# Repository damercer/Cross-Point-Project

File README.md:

# Cross Point Project
Software-Configured Breadboard Hardware Targeting Circuit Wiring Error Reduction in ECE Labs.
#
Abstract:
#
The hardware project aims to examine the effectiveness of software-configured wiring compared to traditional manual wiring of breadboards. While both methods use actual hardware, the software-configured approach automates the connections between components, thereby minimizing wiring errors and setup time. The intent is to investigate the impact of each approach on student comprehension, engagement, and error rates. By comparing these two approaches, the project seeks to determine which method better supports student engagement, educational outcomes and reduces frustration associated with complex circuit construction.
#
Introduction:
#
Hands-on experiential learning is a cornerstone of ECE education, typically relying on manual wiring of circuits on solderless breadboards. Using a traditional solderless breadboard as the means for building electronic circuit lab experiments requires the student, in addition to placing components, to manually insert wires to connect together the component pins according to a schematic diagram. These manual translation steps from schematic to hardware can lead to wiring errors in the experimental setup that can obscure circuit principles. While this manual wiring method offers valuable experience in physical component handling and troubleshooting, the extra time needed for debugging and correcting these errors leads to frustration and loss of precious lab time to investigate the circuit concept in question.

The goal is to evaluate the educational benefits and potential drawbacks of these software-configured hardware systems compared to traditional manual wiring. By doing so, it addresses the need for balancing hands-on skills with error minimization and conceptual understanding in electrical engineering education.
#
Analog switch matrix cross point experiment breadboard.
#

Prototype PCB (Red version)
 
The idea is to computerize the wiring of the breadboard in an effort to reduce student frustration when building complex experiments. Using four analog 16X8 cross point switches wired together into two 32X8 cross points with a fifth switch matrix interconnecting the two smaller arrays into effectively a single 64X16 array.

This breadboard makes real, hardware connections between the 64 breadboard component pins on the board to the16 “jumper” nodes on the board via software commands, instead of needing to manually install jumper wires. The prototype PCB is shown, figure 1, which incorporates two mini 170 pin solderless breadboards, one for each of the 32X8 cross point arrays. There are a combined 68 total component pin locations across both mini breadboards with power distribution strips top and bottom. The two mini breadboards connect to the PCB through pogo pins and so they can be easily removed. It would then be possible to bolt on custom daughter PCBs with whatever components are needed for a given course already installed. Such as CMOS transistor arrays (CD4007) with even some pre-wired sub-circuits like current sources and OTAs.

The combined 64X16 cross point matrix board uses a total of 5 CH446DS 16X8 analog cross point ICs (from China) programed via a RP-2040 micro controller breakout board (Pi Pico or equivalent). Materials cost per board, in quantities of 10 or more, is less than $30 not including the assembly labor.

The board is powered from the Pi Pico USB connection. For powering the experiment circuits, male Pin Jumpers can be set for 0 and +3.3V, 0 and +5V or -5V and +5V power (or 0 and +10V) using an on board isolated 5V DC-DC generator.

LTspice is used to enter the schematic for the experiment. In addition to the standard library symbols a number of supporting schematic library files have been created. Schematic symbols for TO-92 transistors and resistors of various lead spacing are available in the LTspice files.

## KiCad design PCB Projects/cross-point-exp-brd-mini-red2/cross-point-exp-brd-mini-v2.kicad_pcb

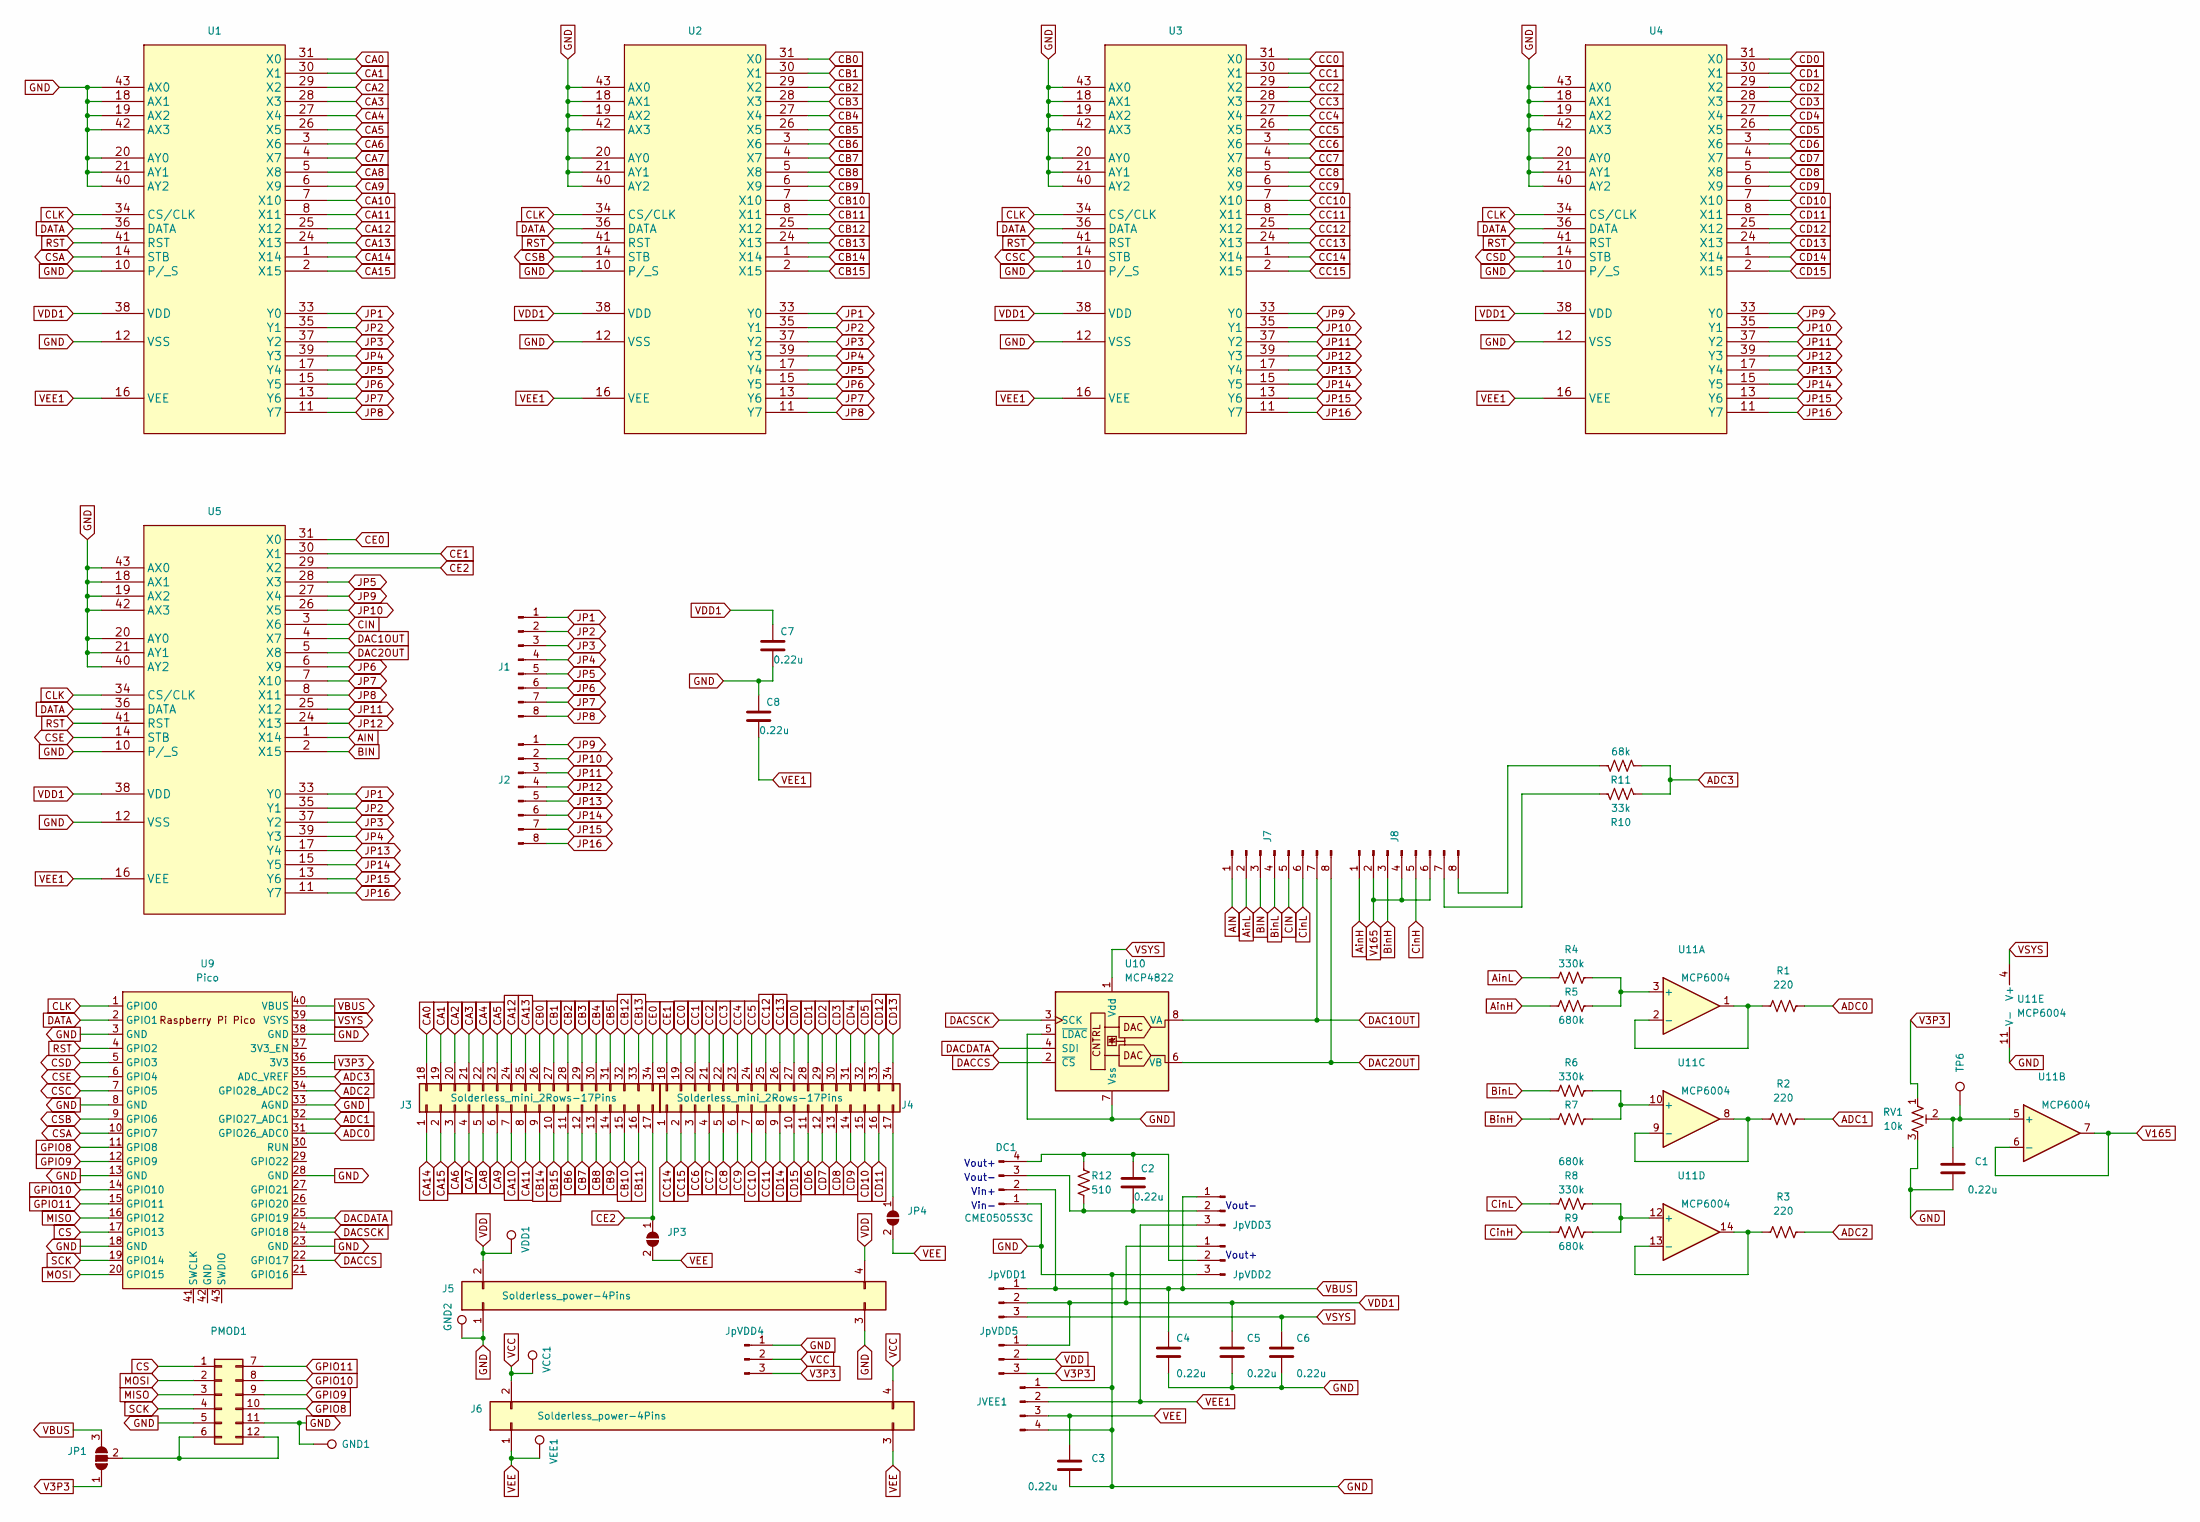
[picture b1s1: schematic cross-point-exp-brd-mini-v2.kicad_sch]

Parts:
C1, C2, C3, C4, C5, C6, C7, C8: 0.22u; C_Rect_L7.0mm_W2.0mm_P5.00mm
DC1: CME0505S3C; PinHeader_1x04_P2.54mm_Vertical
GND1: TestPoint; TestPoint_THTPad_D1.5mm_Drill0.7mm
GND2: TestPoint; TestPoint_THTPad_D2.0mm_Drill1.0mm
J1, J2, J7, J8: Conn_01x08_Pin; PinHeader_1x08_P2.54mm_Vertical
J3, J4: Solderless_mini_2Rows-17Pins; Solderless_mini_th_pogo_2x17_P2.54mm
J5, J6: Solderless_power-4Pins; Solderless_power_2x4_P2.54mm
JP1: SolderJumper_3_Open; SolderJumper-3_P1.3mm_Open_RoundedPad1.0x1.5mm_NumberLabels
JP3, JP4: SolderJumper_2_Open; SolderJumper-2_P1.3mm_Open_RoundedPad1.0x1.5mm
JVEE1: Conn_01x04_Pin; PinHeader_1x04_P2.54mm_Vertical
JpVDD1, JpVDD2, JpVDD3, JpVDD4, JpVDD5: Conn_01x03_Pin; PinHeader_1x03_P2.54mm_Vertical
PMOD1: Conn_02x06_Top_Bottom; PMOD_Header_2x06_P2.54mm
R1, R2, R3: 220; R_Axial_DIN0204_L3.6mm_D1.6mm_P7.62mm_Horizontal
R4, R6, R8: 330k; R_Axial_DIN0204_L3.6mm_D1.6mm_P7.62mm_Horizontal
R5, R7, R9: 680k; R_Axial_DIN0204_L3.6mm_D1.6mm_P7.62mm_Horizontal
R10: 33k; R_Axial_DIN0204_L3.6mm_D1.6mm_P7.62mm_Horizontal
R11: 68k; R_Axial_DIN0204_L3.6mm_D1.6mm_P7.62mm_Horizontal
R12: 510; R_Axial_DIN0204_L3.6mm_D1.6mm_P7.62mm_Horizontal
RV1: 10k; Potentiometer_Bourns_3386P_Vertical
TP6: TestPoint; TestPoint_THTPad_D1.5mm_Drill0.7mm
U1, U2, U3, U4, U5: LQFP44_Tight
U9: Pico; RPi_Pico_SMD_TH
U10: MCP4822; DIP-8_W7.62mm
U11: MCP6004; DIP-14_W7.62mm
VCC1: TestPoint; TestPoint_THTPad_D2.0mm_Drill1.0mm
VDD1: TestPoint; TestPoint_THTPad_D2.0mm_Drill1.0mm
VEE1: TestPoint; TestPoint_THTPad_D2.0mm_Drill1.0mm

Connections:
ADC0: R1.1, U9.31 (GPIO26_ADC0)
ADC1: R2.1, U9.32 (GPIO27_ADC1)
ADC2: R3.1, U9.34 (GPIO28_ADC2)
ADC3: R10.1, R11.1, U9.35 (ADC_VREF)
AIN: J7.1, U5.1 (X14)
AinH: J8.1, R5.2
AinL: J7.2, R4.2
BIN: J7.3, U5.2 (X15)
BinH: J8.3, R7.2
BinL: J7.4, R6.2
CA0: J3.18, U1.31 (X0)
CA1: J3.19, U1.30 (X1)
CA2: J3.20, U1.29 (X2)
CA3: J3.21, U1.28 (X3)
CA4: J3.22, U1.27 (X4)
CA5: J3.23, U1.26 (X5)
CA6: J3.3, U1.3 (X6)
CA7: J3.4, U1.4 (X7)
CA8: J3.5, U1.5 (X8)
CA9: J3.6, U1.6 (X9)
CA10: J3.7, U1.7 (X10)
CA11: J3.8, U1.8 (X11)
CA12: J3.24, U1.25 (X12)
CA13: J3.25, U1.24 (X13)
CA14: J3.1, U1.1 (X14)
CA15: J3.2, U1.2 (X15)
CB0: J3.26, U2.31 (X0)
CB1: J3.27, U2.30 (X1)
CB2: J3.28, U2.29 (X2)
CB3: J3.29, U2.28 (X3)
CB4: J3.30, U2.27 (X4)
CB5: J3.31, U2.26 (X5)
CB6: J3.11, U2.3 (X6)
CB7: J3.12, U2.4 (X7)
CB8: J3.13, U2.5 (X8)
CB9: J3.14, U2.6 (X9)
CB10: J3.15, U2.7 (X10)
CB11: J3.16, U2.8 (X11)
CB12: J3.32, U2.25 (X12)
CB13: J3.33, U2.24 (X13)
CB14: J3.9, U2.1 (X14)
CB15: J3.10, U2.2 (X15)
CC0: J4.19, U3.31 (X0)
CC1: J4.20, U3.30 (X1)
CC2: J4.21, U3.29 (X2)
CC3: J4.22, U3.28 (X3)
CC4: J4.23, U3.27 (X4)
CC5: J4.24, U3.26 (X5)
CC6: J4.3, U3.3 (X6)
CC7: J4.4, U3.4 (X7)
CC8: J4.5, U3.5 (X8)
CC9: J4.6, U3.6 (X9)
CC10: J4.7, U3.7 (X10)
CC11: J4.8, U3.8 (X11)
CC12: J4.25, U3.25 (X12)
CC13: J4.26, U3.24 (X13)
CC14: J4.1, U3.1 (X14)
CC15: J4.2, U3.2 (X15)
CD0: J4.27, U4.31 (X0)
CD1: J4.28, U4.30 (X1)
CD2: J4.29, U4.29 (X2)
CD3: J4.30, U4.28 (X3)
CD4: J4.31, U4.27 (X4)
CD5: J4.32, U4.26 (X5)
CD6: J4.11, U4.3 (X6)
CD7: J4.12, U4.4 (X7)
CD8: J4.13, U4.5 (X8)
CD9: J4.14, U4.6 (X9)
CD10: J4.15, U4.7 (X10)
CD11: J4.16, U4.8 (X11)
CD12: J4.33, U4.25 (X12)
CD13: J4.34, U4.24 (X13)
CD14: J4.9, U4.1 (X14)
CD15: J4.10, U4.2 (X15)
CE0: J3.34, U5.31 (X0)
CE1: J4.18, U5.30 (X1)
CE2: J3.17, JP3.1 (A), U5.29 (X2)
CIN: J7.5, U5.3 (X6)
CLK: U1.34 (CS/CLK), U2.34 (CS/CLK), U3.34 (CS/CLK), U4.34 (CS/CLK), U5.34 (CS/CLK), U9.1 (GPIO0)
CS: PMOD1.1, U9.17 (GPIO13)
CSA: U1.14 (STB), U9.10 (GPIO7)
CSB: U2.14 (STB), U9.9 (GPIO6)
CSC: U3.14 (STB), U9.7 (GPIO5)
CSD: U4.14 (STB), U9.5 (GPIO3)
CSE: U5.14 (STB), U9.6 (GPIO4)
CinH: J8.5, R9.2
CinL: J7.6, R8.2
DAC1OUT: J7.7, U5.4 (X7), U10.8 (VA)
DAC2OUT: J7.8, U5.5 (X8), U10.6 (VB)
DACCS: U9.22 (GPIO17), U10.2 (~CS)
DACDATA: U9.25 (GPIO19), U10.4 (SDI)
DACSCK: U9.24 (GPIO18), U10.3 (SCK)
DATA: U1.36 (DATA), U2.36 (DATA), U3.36 (DATA), U4.36 (DATA), U5.36 (DATA), U9.2 (GPIO1)
GND: C1.2, C3.2, C4.2, C5.2, C6.2, C7.2, C8.1, DC1.1, GND1.1, GND2.1, J5.1, J5.3, JVEE1.1, JVEE1.4, JpVDD2.3, JpVDD4.1, PMOD1.5, PMOD1.11, RV1.3, U1.10 (P/_S), U1.12 (VSS), U1.18 (AX1), U1.19 (AX2), U1.20 (AY0), U1.21 (AY1), U1.40 (AY2), U1.42 (AX3), U1.43 (AX0), U2.10 (P/_S), U2.12 (VSS), U2.18 (AX1), U2.19 (AX2), U2.20 (AY0), U2.21 (AY1), U2.40 (AY2), U2.42 (AX3), U2.43 (AX0), U3.10 (P/_S), U3.12 (VSS), U3.18 (AX1), U3.19 (AX2), U3.20 (AY0), U3.21 (AY1), U3.40 (AY2), U3.42 (AX3), U3.43 (AX0), U4.10 (P/_S), U4.12 (VSS), U4.18 (AX1), U4.19 (AX2), U4.20 (AY0), U4.21 (AY1), U4.40 (AY2), U4.42 (AX3), U4.43 (AX0), U5.10 (P/_S), U5.12 (VSS), U5.18 (AX1), U5.19 (AX2), U5.20 (AY0), U5.21 (AY1), U5.40 (AY2), U5.42 (AX3), U5.43 (AX0), U9.3 (GND), U9.8 (GND), U9.13 (GND), U9.18 (GND), U9.23 (GND), U9.28 (GND), U9.33 (AGND), U9.38 (GND), U10.5 (~LDAC), U10.7 (Vss), U11.11 (V-)
GPIO8: PMOD1.10, U9.11 (GPIO8)
GPIO9: PMOD1.9, U9.12 (GPIO9)
GPIO10: PMOD1.8, U9.14 (GPIO10)
GPIO11: PMOD1.7, U9.15 (GPIO11)
JP1: J1.1, U1.33 (Y0), U2.33 (Y0), U5.33 (Y0)
JP2: J1.2, U1.35 (Y1), U2.35 (Y1), U5.35 (Y1)
JP3: J1.3, U1.37 (Y2), U2.37 (Y2), U5.37 (Y2)
JP4: J1.4, U1.39 (Y3), U2.39 (Y3), U5.39 (Y3)
JP5: J1.5, U1.17 (Y4), U2.17 (Y4), U5.28 (X3)
JP6: J1.6, U1.15 (Y5), U2.15 (Y5), U5.6 (X9)
JP7: J1.7, U1.13 (Y6), U2.13 (Y6), U5.7 (X10)
JP8: J1.8, U1.11 (Y7), U2.11 (Y7), U5.8 (X11)
JP9: J2.1, U3.33 (Y0), U4.33 (Y0), U5.27 (X4)
JP10: J2.2, U3.35 (Y1), U4.35 (Y1), U5.26 (X5)
JP11: J2.3, U3.37 (Y2), U4.37 (Y2), U5.25 (X12)
JP12: J2.4, U3.39 (Y3), U4.39 (Y3), U5.24 (X13)
JP13: J2.5, U3.17 (Y4), U4.17 (Y4), U5.17 (Y4)
JP14: J2.6, U3.15 (Y5), U4.15 (Y5), U5.15 (Y5)
JP15: J2.7, U3.13 (Y6), U4.13 (Y6), U5.13 (Y6)
JP16: J2.8, U3.11 (Y7), U4.11 (Y7), U5.11 (Y7)
MISO: PMOD1.3, U9.16 (GPIO12)
MOSI: PMOD1.2, U9.20 (GPIO15)
unnamed: C2.2, DC1.3, JpVDD3.2, R12.1
unnamed: C2.1, DC1.4, JpVDD2.2, R12.2
unnamed: J4.17, JP4.1 (A)
unnamed: J8.7, R10.2
unnamed: J8.8, R11.2
unnamed: JP1.2 (C), PMOD1.6, PMOD1.12
unnamed: R4.1, R5.1, U11.3 (+)
unnamed: R1.2, U11.1, U11.2 (-)
unnamed: C1.1, RV1.2, TP6.1, U11.5 (+)
unnamed: R6.1, R7.1, U11.10 (+)
unnamed: R2.2, U11.8, U11.9 (-)
unnamed: R8.1, R9.1, U11.12 (+)
unnamed: R3.2, U11.13 (-), U11.14
RST: U1.41 (RST), U2.41 (RST), U3.41 (RST), U4.41 (RST), U5.41 (RST), U9.4 (GPIO2)
SCK: PMOD1.4, U9.19 (GPIO14)
V3P3: JP1.1 (A), JpVDD4.3, JpVDD5.3, RV1.1, U9.36 (3V3)
V165: J8.2, J8.4, J8.6, U11.6 (-), U11.7
VBUS: C4.1, DC1.2, JP1.3 (B), JpVDD1.1, JpVDD3.1, U9.40 (VBUS)
VCC: J6.2, J6.4, JpVDD4.2, VCC1.1
VDD: J5.2, J5.4, JpVDD5.2, VDD1.1
VDD1: C5.1, C7.1, JpVDD1.2, JpVDD2.1, JpVDD5.1, U1.38 (VDD), U2.38 (VDD), U3.38 (VDD), U4.38 (VDD), U5.38 (VDD)
VEE: C3.1, J6.1, J6.3, JP3.2 (B), JP4.2 (B), JVEE1.3, VEE1.1
VEE1: C8.2, JVEE1.2, JpVDD3.3, U1.16 (VEE), U2.16 (VEE), U3.16 (VEE), U4.16 (VEE), U5.16 (VEE)
VSYS: C6.1, JpVDD1.3, U9.39 (VSYS), U10.1 (Vdd), U11.4 (V+)

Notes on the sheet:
Vin+
Vout+
Vout-
Vin-

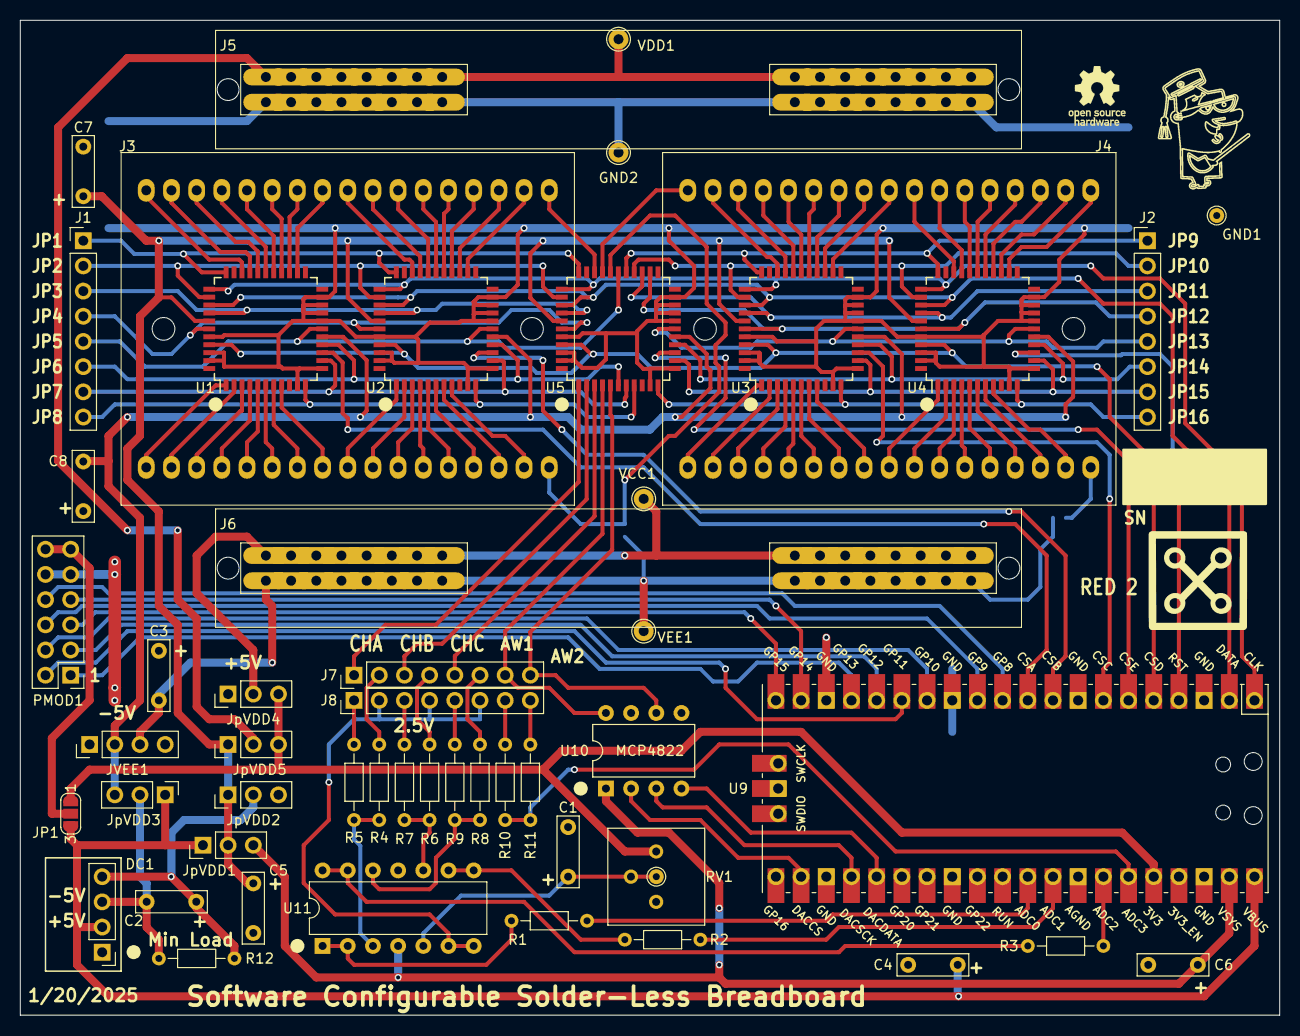
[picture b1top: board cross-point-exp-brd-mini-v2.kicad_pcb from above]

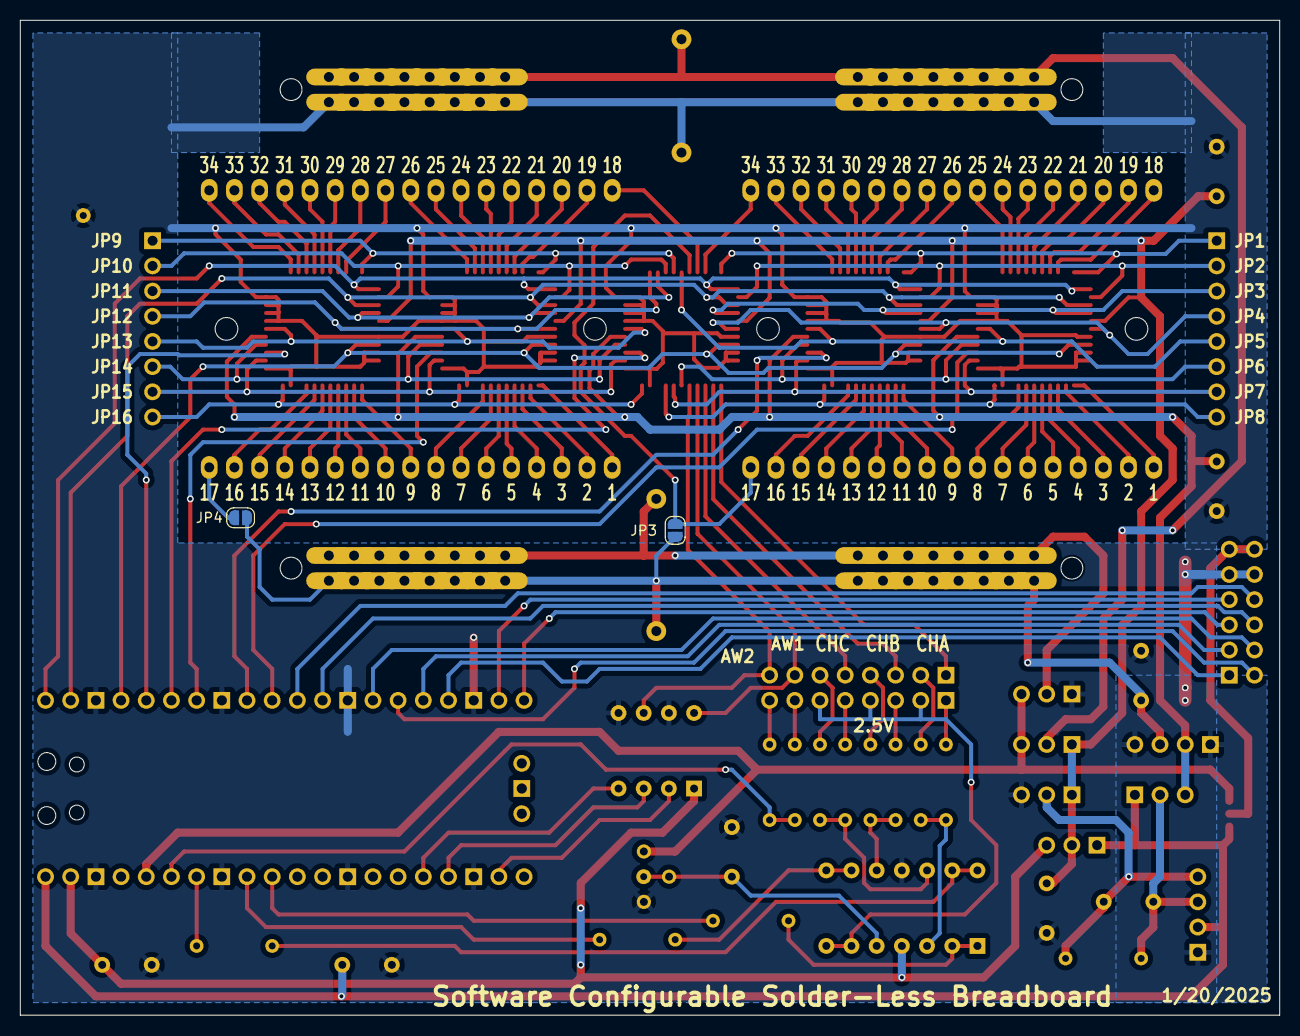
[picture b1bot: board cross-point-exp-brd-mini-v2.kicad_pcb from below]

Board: 2 copper layers, 127.0 x 100.3 mm, 54 parts (2 on the bottom side), 140 nets.

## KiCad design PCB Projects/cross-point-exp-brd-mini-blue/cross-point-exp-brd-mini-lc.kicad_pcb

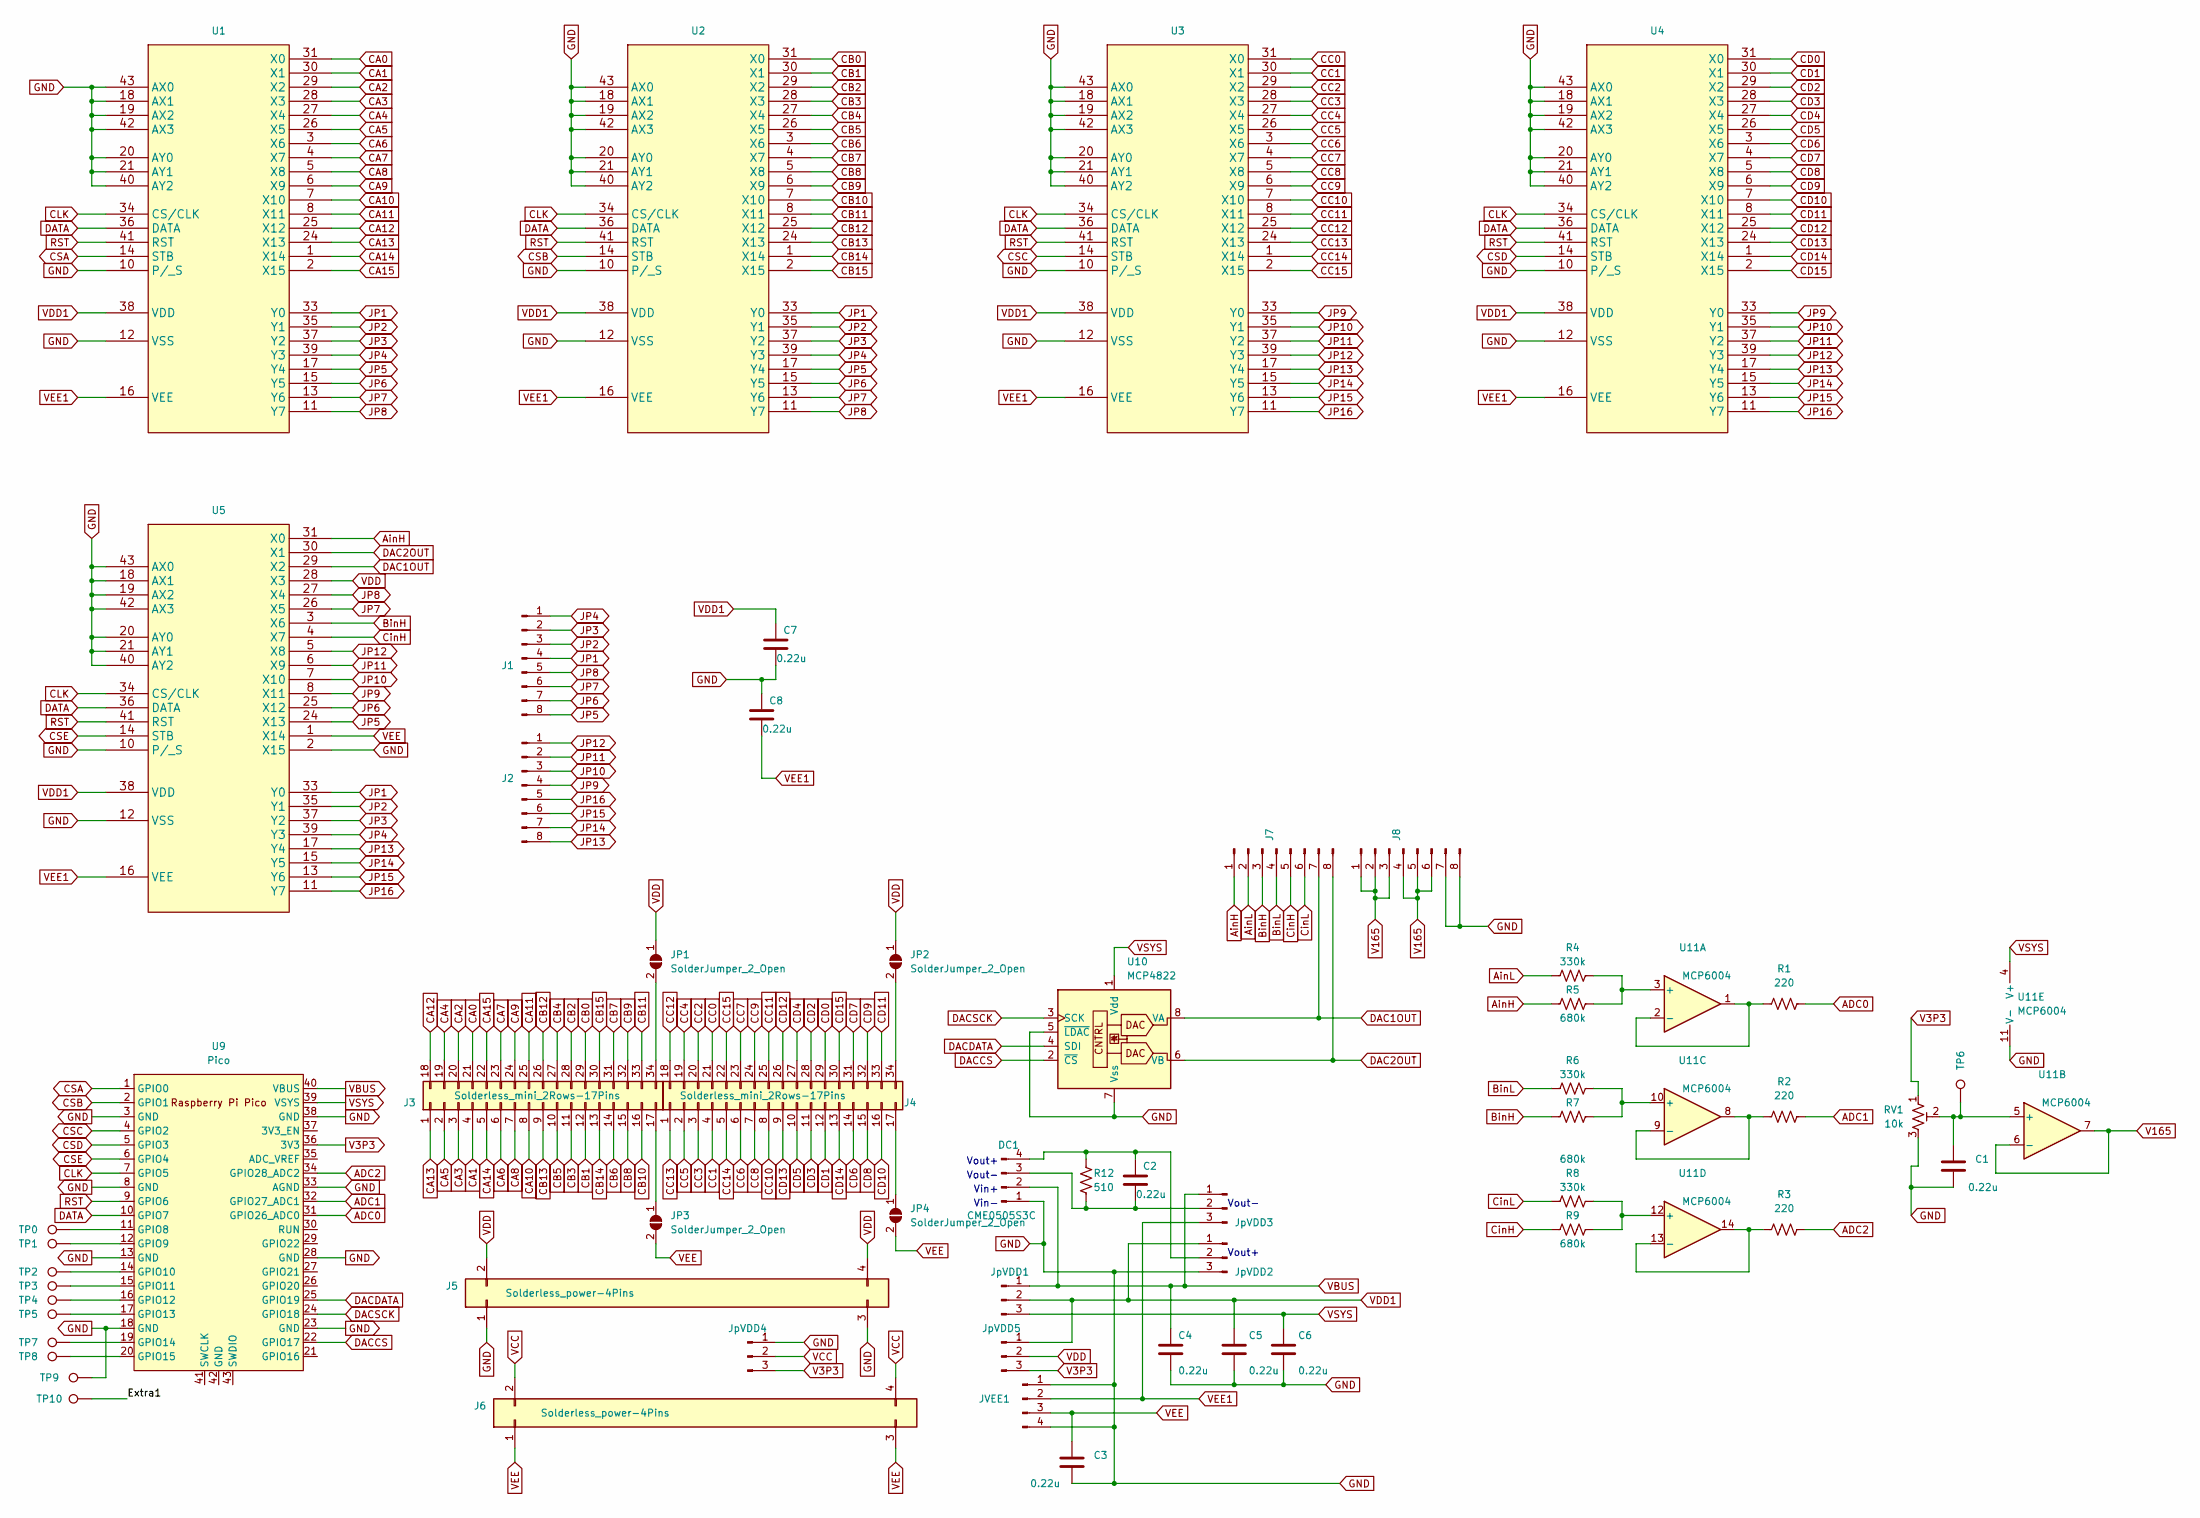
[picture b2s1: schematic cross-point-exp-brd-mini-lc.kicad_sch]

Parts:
C1, C2, C3, C4, C5, C6, C7, C8: 0.22u; C_Rect_L7.0mm_W2.0mm_P5.00mm
DC1: CME0505S3C; PinHeader_1x04_P2.54mm_Vertical
J1, J2, J7, J8: Conn_01x08_Pin; PinHeader_1x08_P2.54mm_Vertical
J3, J4: Solderless_mini_2Rows-17Pins; Solderless_mini_wmh_2x17_P2.54mm
J5, J6: Solderless_power-4Pins; Solderless_power_P2.54mm
JP1, JP2, JP3, JP4: SolderJumper_2_Open; SolderJumper-2_P1.3mm_Open_RoundedPad1.0x1.5mm
JVEE1: Conn_01x04_Pin; PinHeader_1x04_P2.54mm_Vertical
JpVDD1, JpVDD2, JpVDD3, JpVDD4, JpVDD5: Conn_01x03_Pin; PinHeader_1x03_P2.54mm_Vertical
R1, R2, R3: 220; R_Axial_DIN0204_L3.6mm_D1.6mm_P7.62mm_Horizontal
R4, R6, R8: 330k; R_Axial_DIN0204_L3.6mm_D1.6mm_P7.62mm_Horizontal
R5, R7, R9: 680k; R_Axial_DIN0204_L3.6mm_D1.6mm_P7.62mm_Horizontal
R12: 510; R_Axial_DIN0204_L3.6mm_D1.6mm_P7.62mm_Horizontal
RV1: 10k; Potentiometer_Bourns_3386P_Vertical
TP0, TP1, TP2, TP3, TP4, TP5, TP6, TP7, TP8, TP9, TP10: TestPoint; TestPoint_THTPad_D1.5mm_Drill0.7mm
U1, U2, U3, U4, U5: LQFP44_Tight
U9: Pico; RPi_Pico_SMD_TH
U10: MCP4822; DIP-8_W7.62mm
U11: MCP6004; DIP-14_W7.62mm

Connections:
/Extra1: TP10.1
ADC0: R1.1, U9.31 (GPIO26_ADC0)
ADC1: R2.1, U9.32 (GPIO27_ADC1)
ADC2: R3.1, U9.34 (GPIO28_ADC2)
AinH: J7.1, R5.2, U5.31 (X0)
AinL: J7.2, R4.2
BinH: J7.3, R7.2, U5.3 (X6)
BinL: J7.4, R6.2
CA0: J3.21, U1.31 (X0)
CA1: J3.4, U1.30 (X1)
CA2: J3.20, U1.29 (X2)
CA3: J3.3, U1.28 (X3)
CA4: J3.19, U1.27 (X4)
CA5: J3.2, U1.26 (X5)
CA6: J3.6, U1.3 (X6)
CA7: J3.23, U1.4 (X7)
CA8: J3.7, U1.5 (X8)
CA9: J3.24, U1.6 (X9)
CA10: J3.8, U1.7 (X10)
CA11: J3.25, U1.8 (X11)
CA12: J3.18, U1.25 (X12)
CA13: J3.1, U1.24 (X13)
CA14: J3.5, U1.1 (X14)
CA15: J3.22, U1.2 (X15)
CB0: J3.29, U2.31 (X0)
CB1: J3.12, U2.30 (X1)
CB2: J3.28, U2.29 (X2)
CB3: J3.11, U2.28 (X3)
CB4: J3.27, U2.27 (X4)
CB5: J3.10, U2.26 (X5)
CB6: J3.14, U2.3 (X6)
CB7: J3.31, U2.4 (X7)
CB8: J3.15, U2.5 (X8)
CB9: J3.32, U2.6 (X9)
CB10: J3.16, U2.7 (X10)
CB11: J3.33, U2.8 (X11)
CB12: J3.26, U2.25 (X12)
CB13: J3.9, U2.24 (X13)
CB14: J3.13, U2.1 (X14)
CB15: J3.30, U2.2 (X15)
CC0: J4.21, U3.31 (X0)
CC1: J4.4, U3.30 (X1)
CC2: J4.20, U3.29 (X2)
CC3: J4.3, U3.28 (X3)
CC4: J4.19, U3.27 (X4)
CC5: J4.2, U3.26 (X5)
CC6: J4.6, U3.3 (X6)
CC7: J4.23, U3.4 (X7)
CC8: J4.7, U3.5 (X8)
CC9: J4.24, U3.6 (X9)
CC10: J4.8, U3.7 (X10)
CC11: J4.25, U3.8 (X11)
CC12: J4.18, U3.25 (X12)
CC13: J4.1, U3.24 (X13)
CC14: J4.5, U3.1 (X14)
CC15: J4.22, U3.2 (X15)
CD0: J4.29, U4.31 (X0)
CD1: J4.12, U4.30 (X1)
CD2: J4.28, U4.29 (X2)
CD3: J4.11, U4.28 (X3)
CD4: J4.27, U4.27 (X4)
CD5: J4.10, U4.26 (X5)
CD6: J4.14, U4.3 (X6)
CD7: J4.31, U4.4 (X7)
CD8: J4.15, U4.5 (X8)
CD9: J4.32, U4.6 (X9)
CD10: J4.16, U4.7 (X10)
CD11: J4.33, U4.8 (X11)
CD12: J4.26, U4.25 (X12)
CD13: J4.9, U4.24 (X13)
CD14: J4.13, U4.1 (X14)
CD15: J4.30, U4.2 (X15)
CLK: U1.34 (CS/CLK), U2.34 (CS/CLK), U3.34 (CS/CLK), U4.34 (CS/CLK), U5.34 (CS/CLK), U9.7 (GPIO5)
CSA: U1.14 (STB), U9.1 (GPIO0)
CSB: U2.14 (STB), U9.2 (GPIO1)
CSC: U3.14 (STB), U9.4 (GPIO2)
CSD: U4.14 (STB), U9.5 (GPIO3)
CSE: U5.14 (STB), U9.6 (GPIO4)
CinH: J7.5, R9.2, U5.4 (X7)
CinL: J7.6, R8.2
DAC1OUT: J7.7, U5.29 (X2), U10.8 (VA)
DAC2OUT: J7.8, U5.30 (X1), U10.6 (VB)
DACCS: U9.22 (GPIO17), U10.2 (~CS)
DACDATA: U9.25 (GPIO19), U10.4 (SDI)
DACSCK: U9.24 (GPIO18), U10.3 (SCK)
DATA: U1.36 (DATA), U2.36 (DATA), U3.36 (DATA), U4.36 (DATA), U5.36 (DATA), U9.10 (GPIO7)
GND: C1.2, C3.2, C4.2, C5.2, C6.2, C7.2, C8.1, DC1.1, J5.1, J5.3, J8.7, J8.8, JVEE1.1, JVEE1.4, JpVDD2.3, JpVDD4.1, RV1.3, TP9.1, U1.10 (P/_S), U1.12 (VSS), U1.18 (AX1), U1.19 (AX2), U1.20 (AY0), U1.21 (AY1), U1.40 (AY2), U1.42 (AX3), U1.43 (AX0), U2.10 (P/_S), U2.12 (VSS), U2.18 (AX1), U2.19 (AX2), U2.20 (AY0), U2.21 (AY1), U2.40 (AY2), U2.42 (AX3), U2.43 (AX0), U3.10 (P/_S), U3.12 (VSS), U3.18 (AX1), U3.19 (AX2), U3.20 (AY0), U3.21 (AY1), U3.40 (AY2), U3.42 (AX3), U3.43 (AX0), U4.10 (P/_S), U4.12 (VSS), U4.18 (AX1), U4.19 (AX2), U4.20 (AY0), U4.21 (AY1), U4.40 (AY2), U4.42 (AX3), U4.43 (AX0), U5.2 (X15), U5.10 (P/_S), U5.12 (VSS), U5.18 (AX1), U5.19 (AX2), U5.20 (AY0), U5.21 (AY1), U5.40 (AY2), U5.42 (AX3), U5.43 (AX0), U9.3 (GND), U9.8 (GND), U9.13 (GND), U9.18 (GND), U9.23 (GND), U9.28 (GND), U9.33 (AGND), U9.38 (GND), U10.5 (~LDAC), U10.7 (Vss), U11.11 (V-)
JP1: J1.4, U1.33 (Y0), U2.33 (Y0), U5.33 (Y0)
JP2: J1.3, U1.35 (Y1), U2.35 (Y1), U5.35 (Y1)
JP3: J1.2, U1.37 (Y2), U2.37 (Y2), U5.37 (Y2)
JP4: J1.1, U1.39 (Y3), U2.39 (Y3), U5.39 (Y3)
JP5: J1.8, U1.17 (Y4), U2.17 (Y4), U5.24 (X13)
JP6: J1.7, U1.15 (Y5), U2.15 (Y5), U5.25 (X12)
JP7: J1.6, U1.13 (Y6), U2.13 (Y6), U5.26 (X5)
JP8: J1.5, U1.11 (Y7), U2.11 (Y7), U5.27 (X4)
JP9: J2.4, U3.33 (Y0), U4.33 (Y0), U5.8 (X11)
JP10: J2.3, U3.35 (Y1), U4.35 (Y1), U5.7 (X10)
JP11: J2.2, U3.37 (Y2), U4.37 (Y2), U5.6 (X9)
JP12: J2.1, U3.39 (Y3), U4.39 (Y3), U5.5 (X8)
JP13: J2.8, U3.17 (Y4), U4.17 (Y4), U5.17 (Y4)
JP14: J2.7, U3.15 (Y5), U4.15 (Y5), U5.15 (Y5)
JP15: J2.6, U3.13 (Y6), U4.13 (Y6), U5.13 (Y6)
JP16: J2.5, U3.11 (Y7), U4.11 (Y7), U5.11 (Y7)
unnamed: C2.2, DC1.3, JpVDD3.2, R12.1
unnamed: C2.1, DC1.4, JpVDD2.2, R12.2
unnamed: J3.17, JP3.1 (A)
unnamed: J3.34, JP1.2 (B)
unnamed: J4.17, JP4.1 (A)
unnamed: J4.34, JP2.2 (B)
unnamed: TP0.1, U9.11 (GPIO8)
unnamed: TP1.1, U9.12 (GPIO9)
unnamed: TP2.1, U9.14 (GPIO10)
unnamed: TP3.1, U9.15 (GPIO11)
unnamed: TP4.1, U9.16 (GPIO12)
unnamed: TP5.1, U9.17 (GPIO13)
unnamed: TP7.1, U9.19 (GPIO14)
unnamed: TP8.1, U9.20 (GPIO15)
unnamed: R4.1, R5.1, U11.3 (+)
unnamed: R1.2, U11.1, U11.2 (-)
unnamed: C1.1, RV1.2, TP6.1, U11.5 (+)
unnamed: R6.1, R7.1, U11.10 (+)
unnamed: R2.2, U11.8, U11.9 (-)
unnamed: R8.1, R9.1, U11.12 (+)
unnamed: R3.2, U11.13 (-), U11.14
RST: U1.41 (RST), U2.41 (RST), U3.41 (RST), U4.41 (RST), U5.41 (RST), U9.9 (GPIO6)
V3P3: JpVDD4.3, JpVDD5.3, RV1.1, U9.36 (3V3)
V165: J8.1, J8.2, J8.3, J8.4, J8.5, J8.6, U11.6 (-), U11.7
VBUS: C4.1, DC1.2, JpVDD1.1, JpVDD3.1, U9.40 (VBUS)
VCC: J6.2, J6.4, JpVDD4.2
VDD: J5.2, J5.4, JP1.1 (A), JP2.1 (A), JpVDD5.2, U5.28 (X3)
VDD1: C5.1, C7.1, JpVDD1.2, JpVDD2.1, JpVDD5.1, U1.38 (VDD), U2.38 (VDD), U3.38 (VDD), U4.38 (VDD), U5.38 (VDD)
VEE: C3.1, J6.1, J6.3, JP3.2 (B), JP4.2 (B), JVEE1.3, U5.1 (X14)
VEE1: C8.2, JVEE1.2, JpVDD3.3, U1.16 (VEE), U2.16 (VEE), U3.16 (VEE), U4.16 (VEE), U5.16 (VEE)
VSYS: C6.1, JpVDD1.3, U9.39 (VSYS), U10.1 (Vdd), U11.4 (V+)

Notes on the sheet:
Vin+
Vout+
Vout-
Vin-

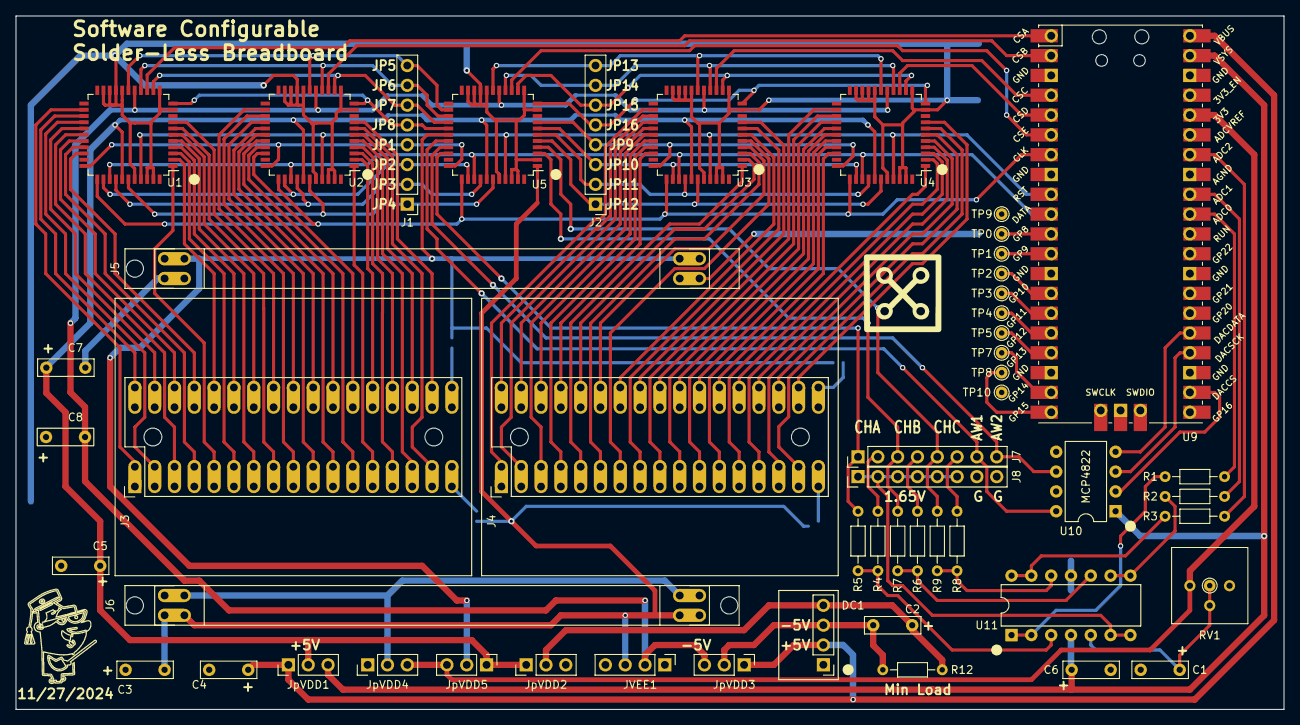
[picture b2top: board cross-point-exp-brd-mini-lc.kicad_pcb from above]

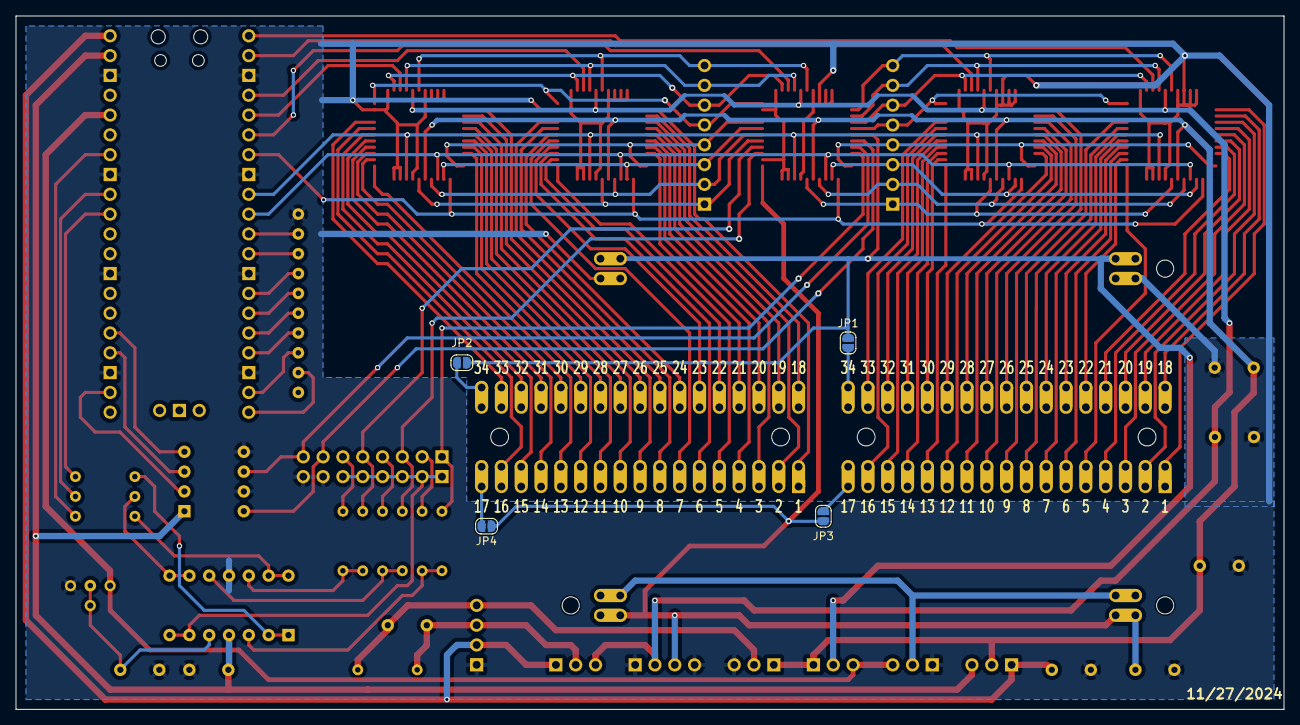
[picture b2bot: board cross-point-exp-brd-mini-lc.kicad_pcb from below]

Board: 2 copper layers, 162.6 x 88.9 mm, 57 parts (4 on the bottom side), 133 nets.

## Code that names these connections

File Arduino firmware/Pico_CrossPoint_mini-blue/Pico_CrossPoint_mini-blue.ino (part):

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  
  Serial.begin(2000000);
  pinMode(led, OUTPUT);
  pinMode(0, OUTPUT); // CSA strobe for switch chip A 
  pinMode(1, OUTPUT); // CSB strobe for switch chip B 
  pinMode(2, OUTPUT); // CSC strobe for switch chip C
  pinMode(3, OUTPUT); // CSD strobe for switch chip D 
  pinMode(4, OUTPUT); // CSE strobe for switch chip E 
  pinMode(5, OUTPUT); // common Clock input
  pinMode(6, OUTPUT); // common Reset input
  pinMode(7, OUTPUT); // common Data input
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
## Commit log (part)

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2025-02-12 Update README.md
    Fix typo in board image line.
2025-02-13 Create LICENSE
    Add License file.
2026-03-22 added chat box to appear in UI
